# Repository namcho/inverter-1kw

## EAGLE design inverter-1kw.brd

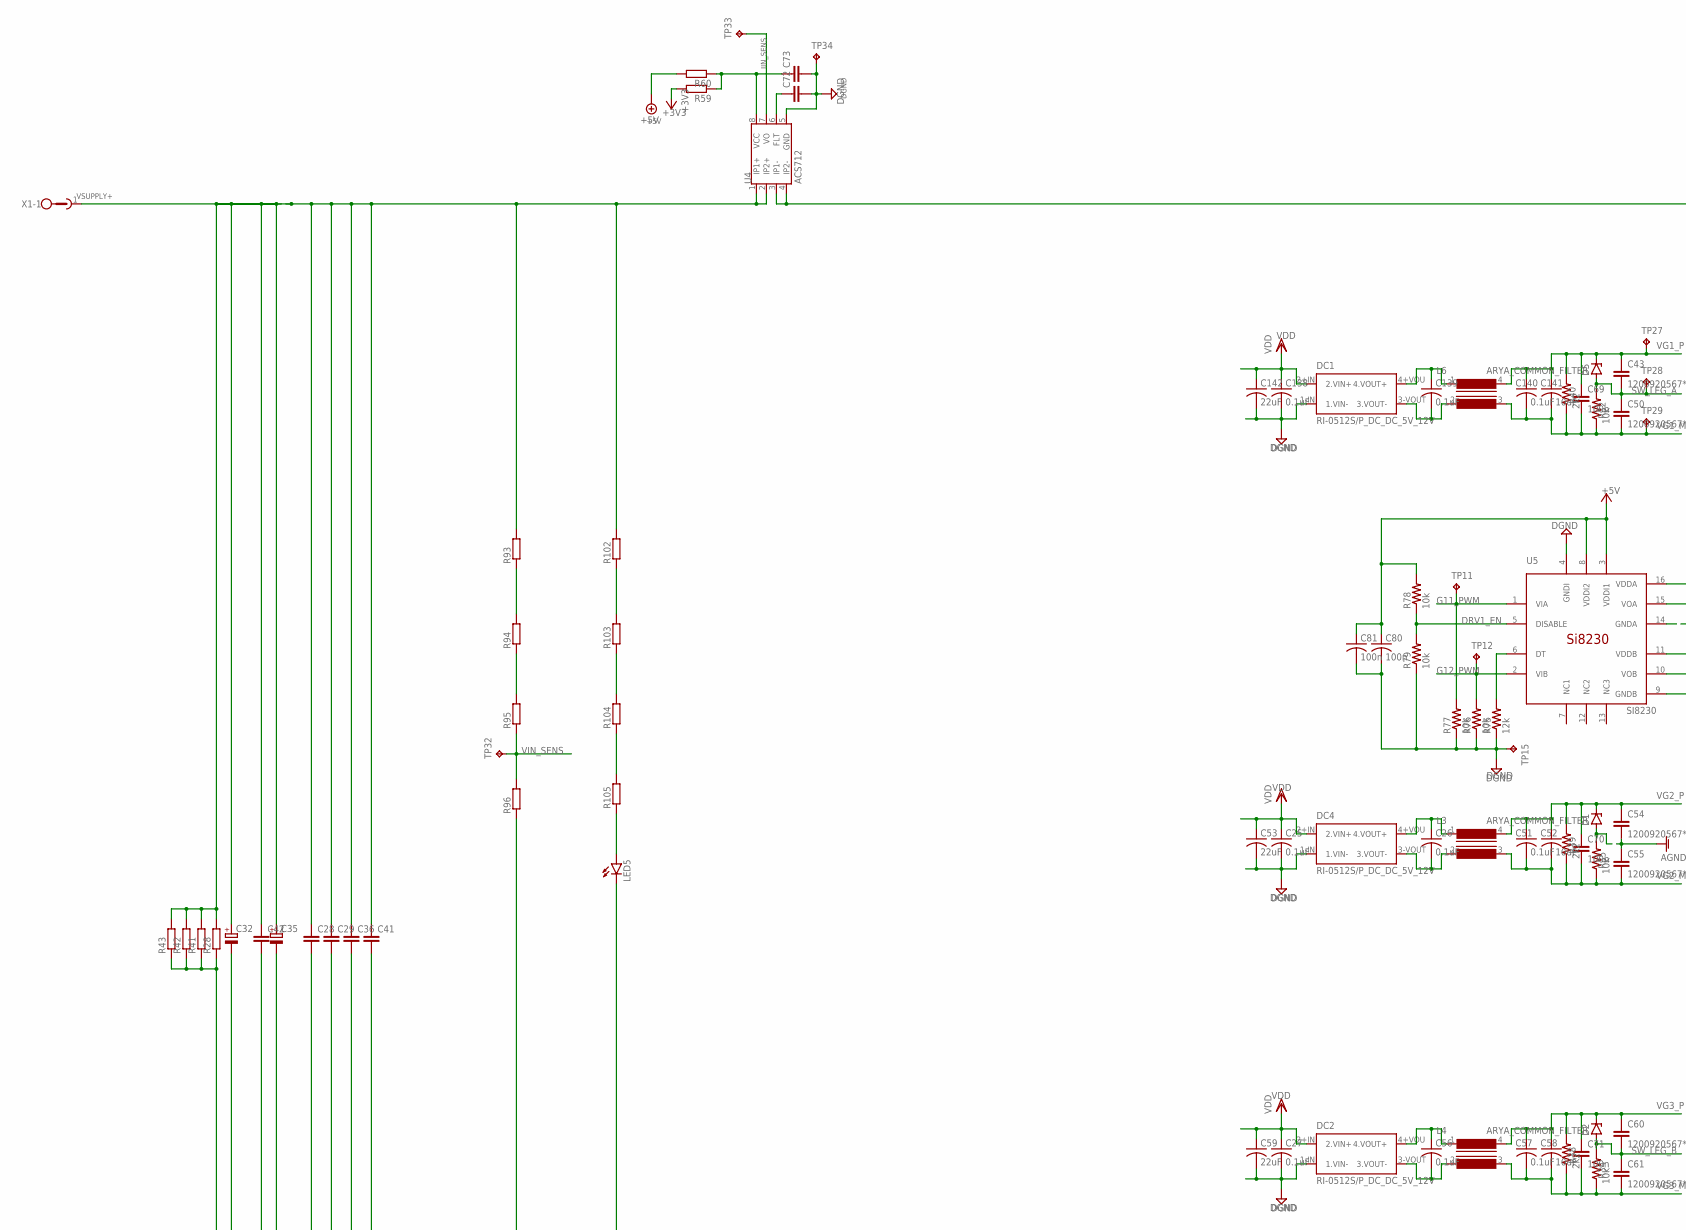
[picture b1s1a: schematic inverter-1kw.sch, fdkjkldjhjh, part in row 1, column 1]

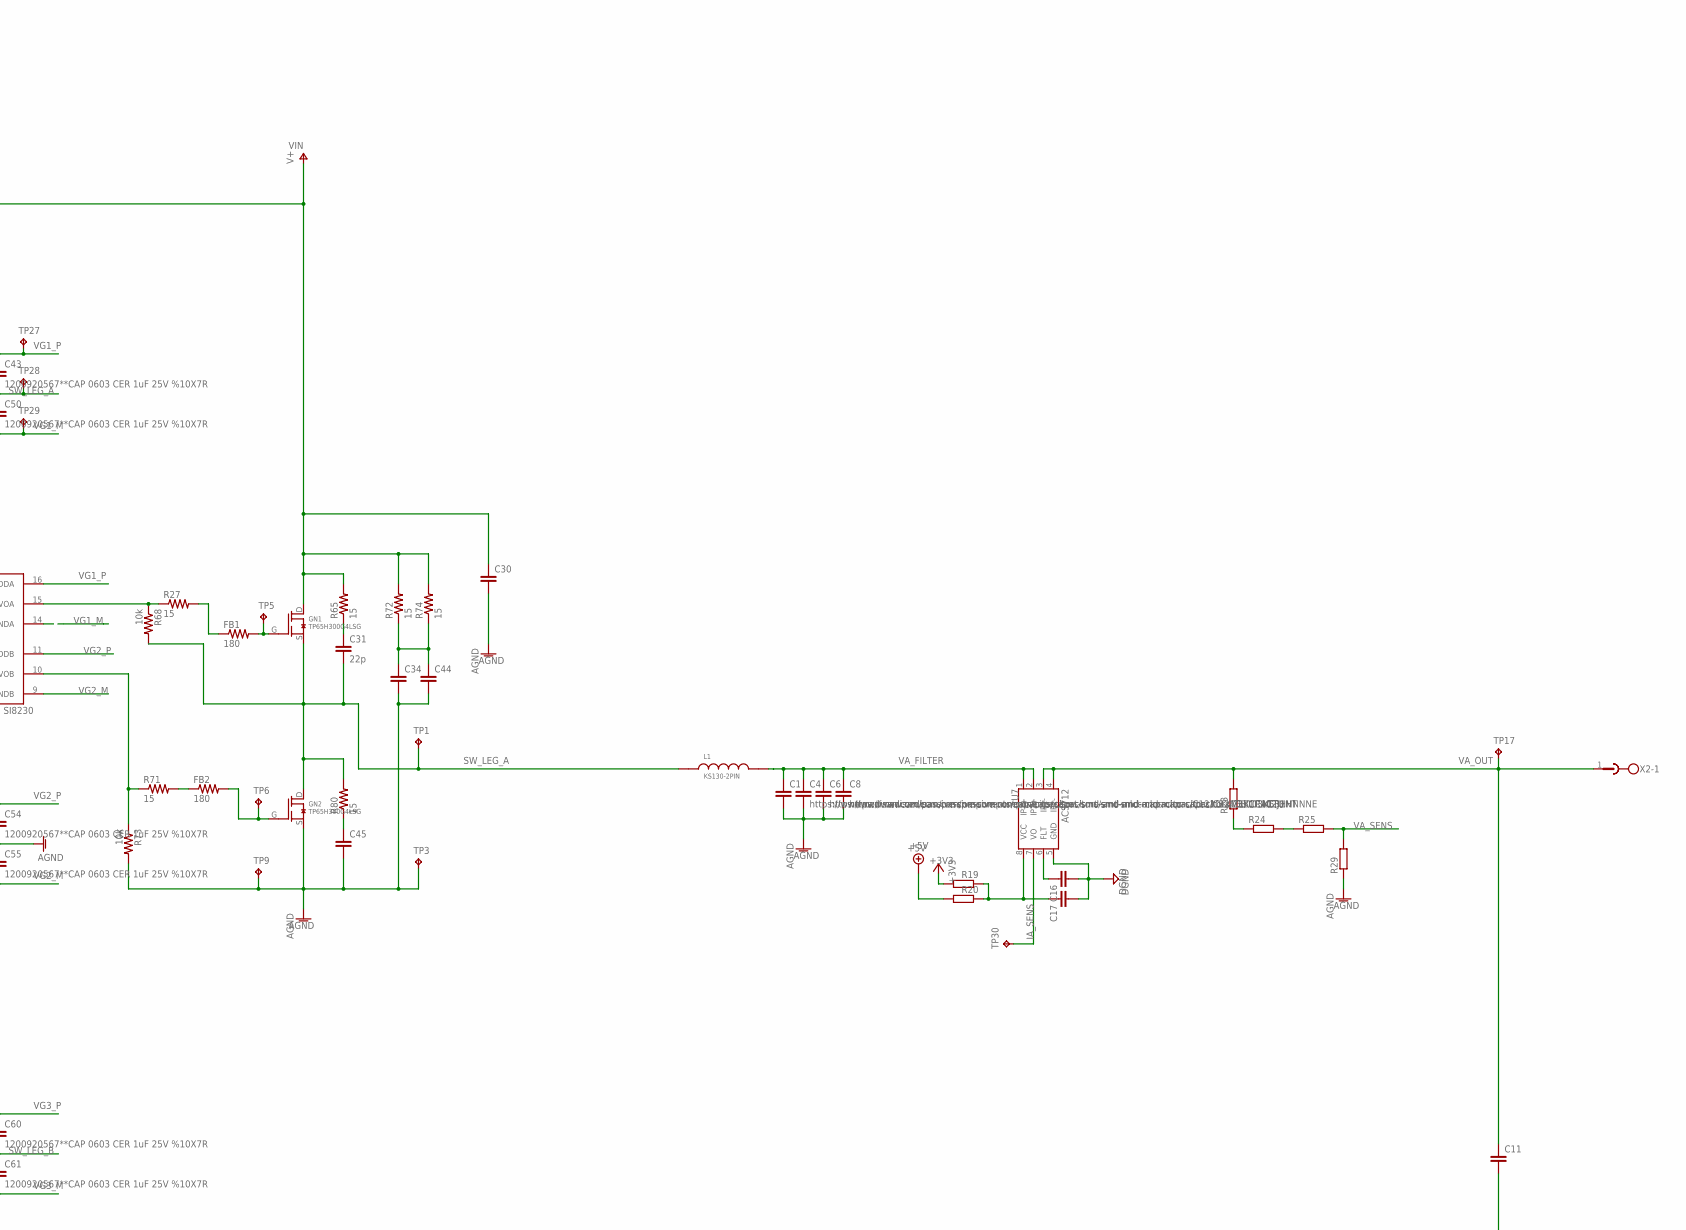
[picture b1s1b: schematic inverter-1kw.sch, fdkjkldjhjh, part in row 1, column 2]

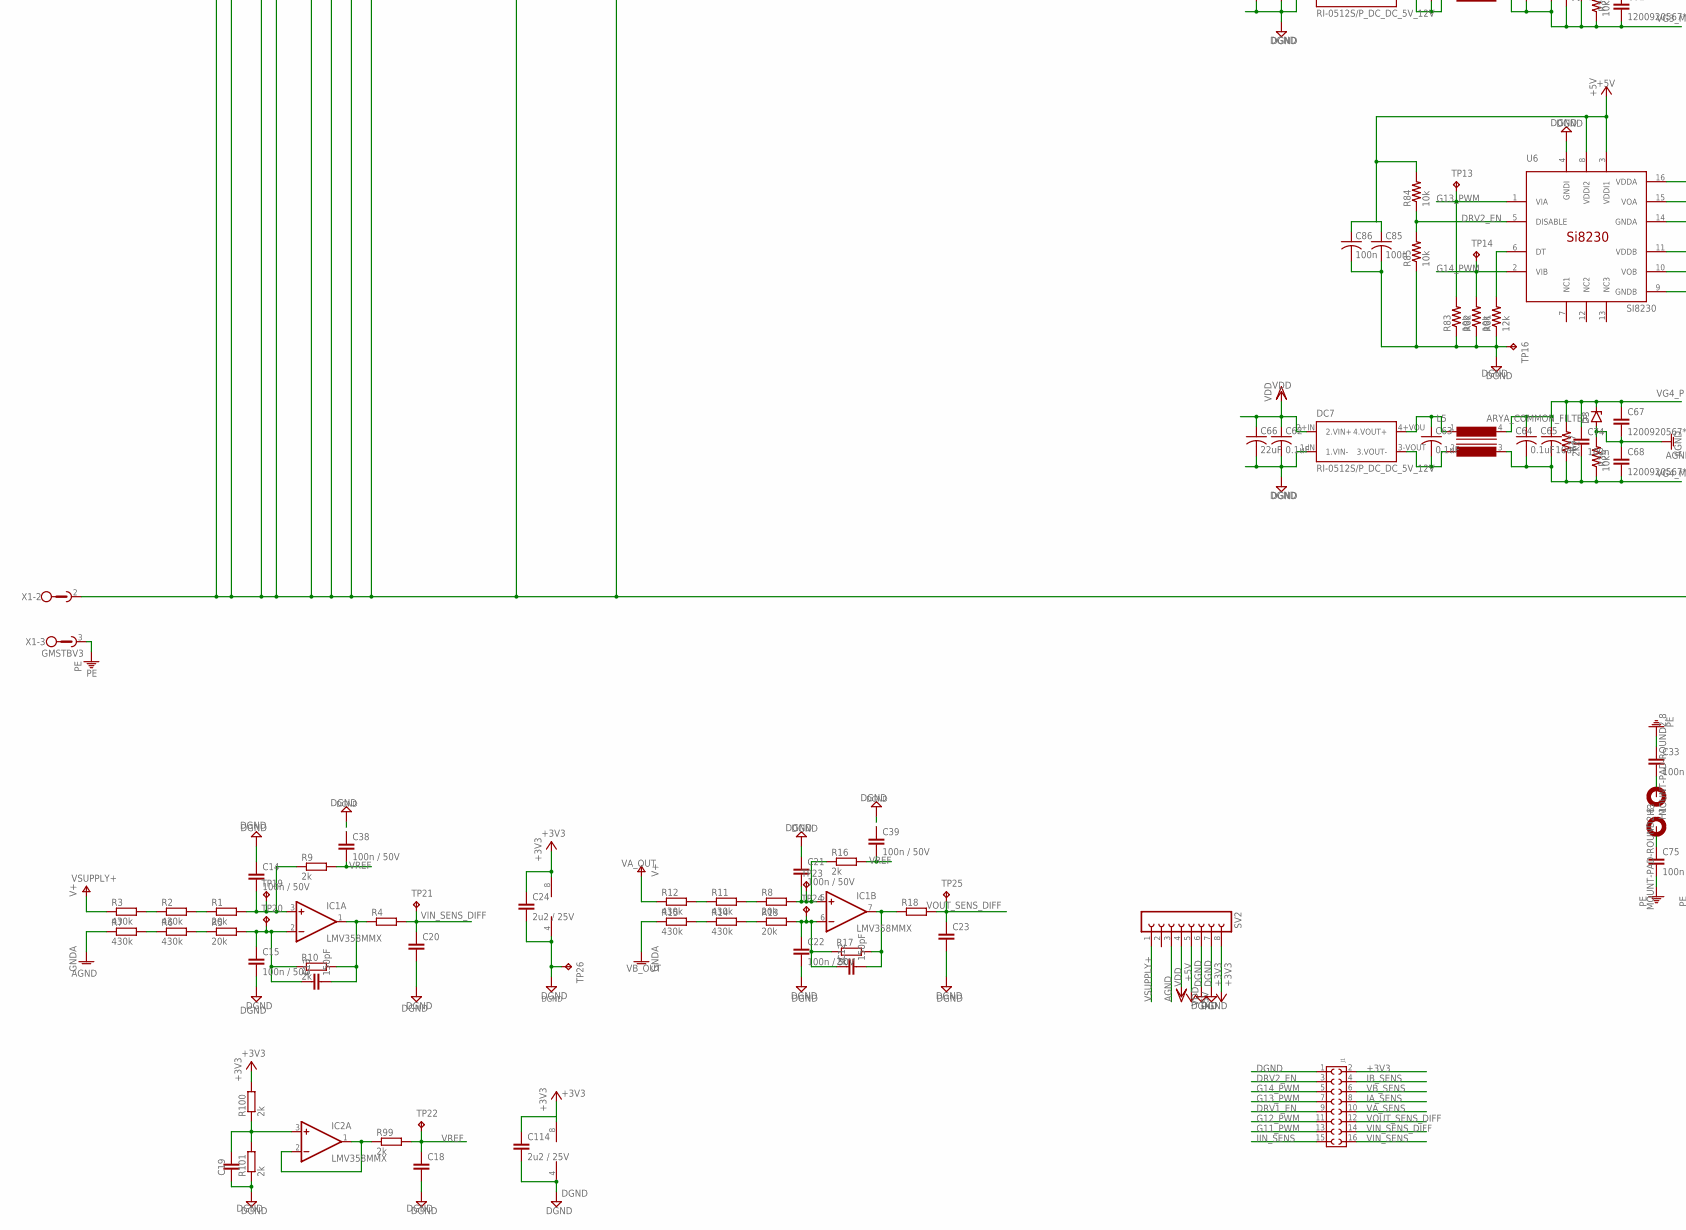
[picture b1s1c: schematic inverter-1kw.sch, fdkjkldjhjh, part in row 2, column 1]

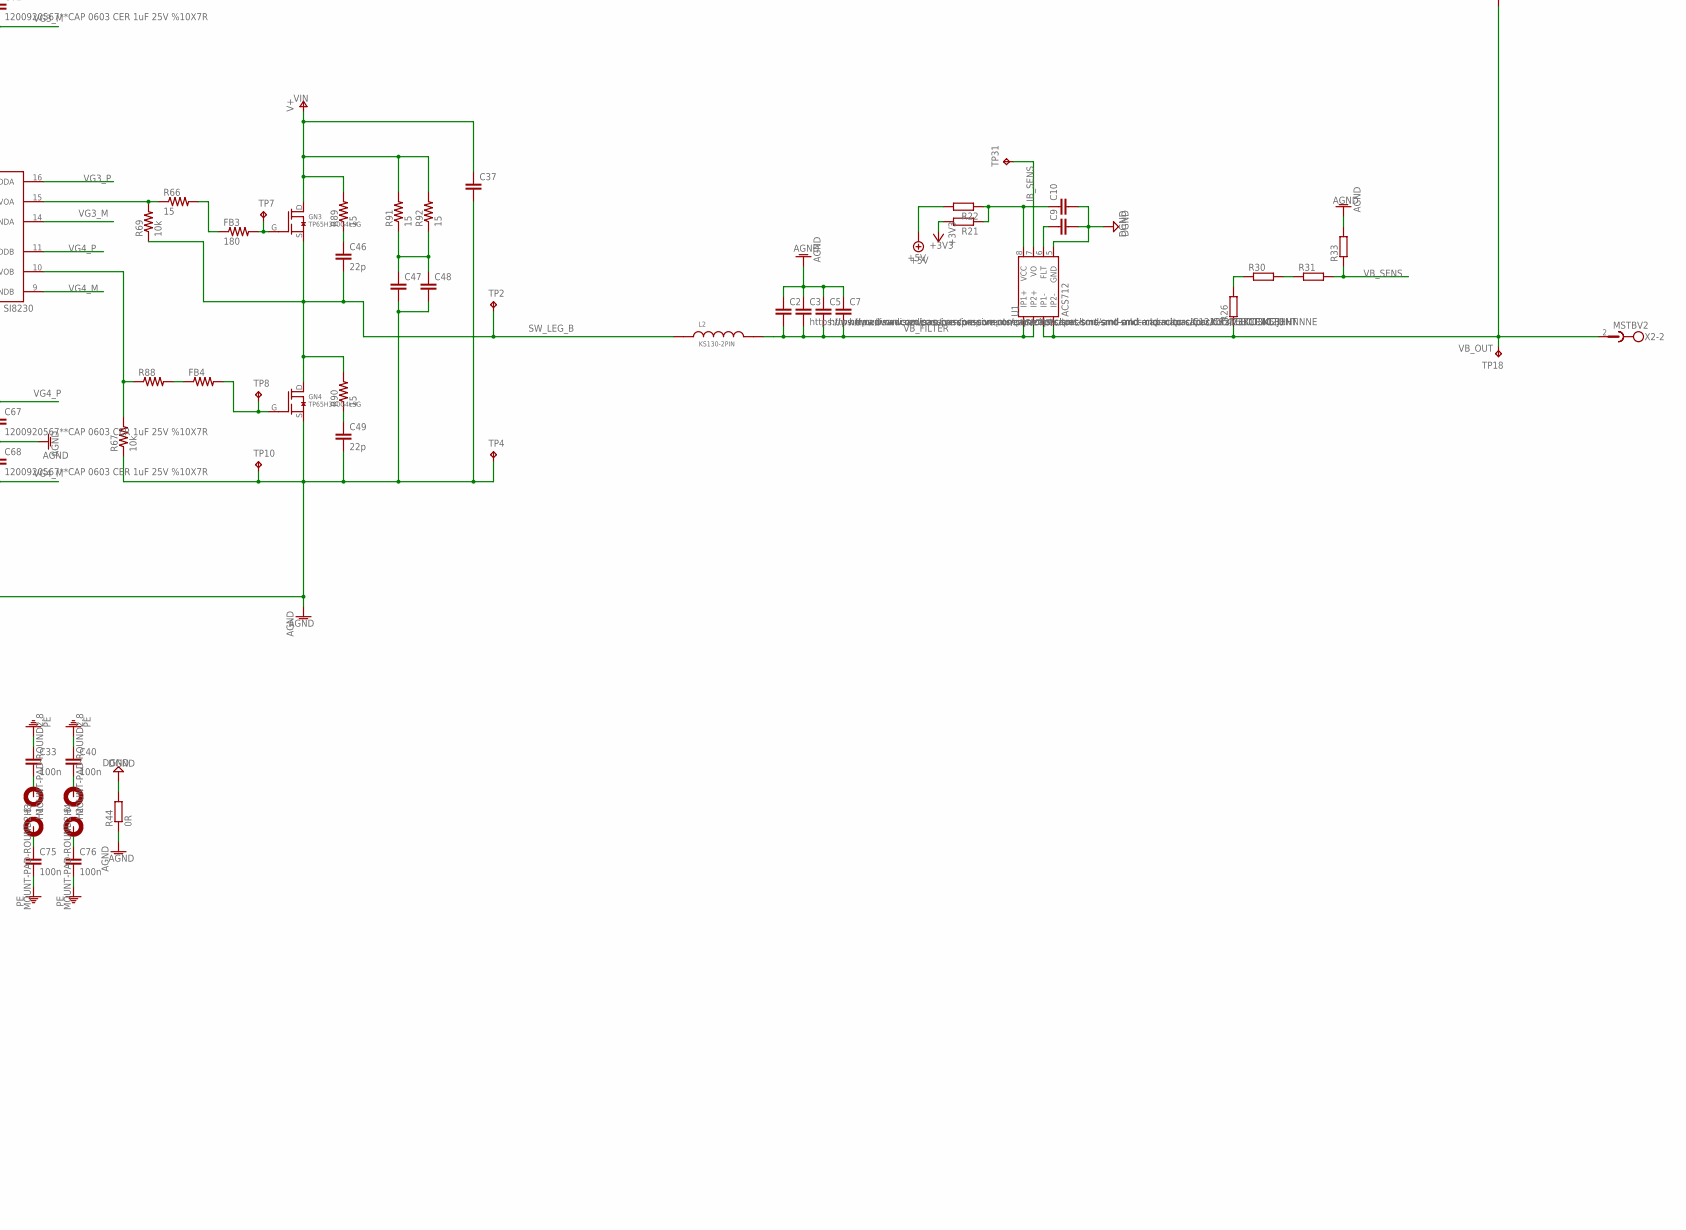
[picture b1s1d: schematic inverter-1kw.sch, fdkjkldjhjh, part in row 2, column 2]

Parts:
C1, C2: C-EUC2225K; C2225K
C3, C4: https://www.ozdisan.com/passive-components/capaci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; C1210K
C5, C6, C7, C8: https://www.ozdisan.com/passive-components/capaci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; C1206
C9, C10, C16, C17, C18, C19, C20, C23, C72, C73: C-EUC0603; C0603
C11: C27/17; C27.5B17
C12, C13: 150pF; C0603
C14, C15, C21, C22, C38, C39: 100n / 50V; C0603
C24, C114: 2u2 / 25V; C0603
C25, C26, C27, C51, C56, C57, C62, C63, C64, C138, C139, C140: 0.1uF; C0603
C28, C29, C30, C36, C37, C41, C42: C-EUC2220K; C2220K
C31, C46, C49: 22p; C1206
C32, C35: CPOL-EUE7.5-18; E7,5-18
C33, C40, C75, C76: 100n; C0805
C34, C44, C45, C47, C48: C-EUC1206; C1206
C43, C50, C54, C55, C60, C61, C67, C68: 1200920567**CAP 0603 CER 1uF 25V %10X7R; C0603K
C52, C58, C65, C141: 10uF; C0805
C53, C59, C66, C142: 22uF; C1206
C69, C70, C71, C74: 100n; C0603K
C80, C81, C85, C86: 100n; C0603
D1, D2, D3, D5: ZENER-DIODESOD80C; SOD80C
DC1, DC2, DC4, DC7: RI-0512S/P_DC_DC_5V_12V
FB1, FB2, FB3: 180; R0603
FB4: R-US_R0603; R0603
GN1, GN2, GN3, GN4: TP65H300G4LSG
H1, H2, H3, H4: MOUNT-PAD-ROUND2.8; 2,8-PAD
IC1, IC2: LMV358MMX; MSOP08
J1: 6230XX21021_62301621021; 62301621021
L1, L2: KS130-2PIN
L3, L4, L5, L6: ARYA_COMMON_FILTER
LED5: LEDCHIPLED_0805; CHIPLED_0805
R1, R5, R8, R13: 20k; R1206
R2, R3, R6, R7, R11, R12, R14, R15: 430k; R1206
R4, R18, R19, R20, R21, R22, R59, R60: R-EU_R0603; R0603
R9, R10, R16, R17, R99, R100, R101: 2k; R0603
R23, R24, R25, R26, R28, R29, R30, R31, R33, R41, R42, R43, R93, R94, R95, R96, R102, R103, R104, R105: R-EU_R1206; R1206
R27, R66, R71: 15; R0603
R32, R34, R35, R36, R67, R68, R69, R73, R76, R77, R78, R79, R82, R83, R84, R85: 10k; R0603
R37, R38, R39, R40: 2k2; R0603
R44: 0R; R1206
R65, R72, R74, R80, R89, R90, R91, R92: 15; R1206
R75, R81: 12k; R0603
R88: R-US_R0603; R0603
SV2: FE08-1; FE08
TP1, TP2, TP3, TP4, TP17, TP18: TPTP17R; TP17R
TP5, TP6, TP7, TP8, TP9, TP10, TP11, TP12, TP13, TP14, TP15, TP16, TP19, TP20, TP21, TP22, TP23, TP24, TP25, TP26, TP27, TP28, TP29, TP30, TP31, TP32, TP33, TP34: TPTP06R; TP06R
U1, U4, U7: ACS712; SOIC8
U5, U6: SI8230; SI8230-N
X1: GMSTBV3
X2: MSTBV2

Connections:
+3V3: C24.1, C114.1, IC1.8 (V+), IC2.8 (V+), J1.2, R19.2, R21.2, R59.2, R100.2, SV2.8
+5V: C80.1, C81.1, C85.1, C86.1, R20.2, R22.2, R60.2, R78.2, R84.2, SV2.5, U5.3 (VDDI1), U5.8 (VDDI2), U6.3 (VDDI1), U6.8 (VDDI2)
AGND: C1.2, C2.1, C3.1, C4.2, C5.1, C6.2, C7.1, C8.2, C28.2, C29.2, C30.2, C32.-, C34.2, C35.-, C36.2, C37.2, C41.2, C42.2, C44.2, C45.2, C47.2, C48.2, C49.2, C54.2, C55.1, C67.2, C68.1, D1.A, D3.A, GN2.S, GN4.S, LED5.C, R7.1, R28.1, R29.1, R33.2, R35.2, R36.2, R41.1, R42.1, R43.1, R44.1, R67.1, R73.2, R96.1, SV2.3, TP3.TP, TP4.TP, TP9.TP, TP10.TP, X1.2
DGND: C9.2, C10.2, C14.1, C15.2, C16.2, C17.2, C18.2, C19.2, C20.2, C21.1, C22.2, C23.2, C24.2, C25.2, C27.2, C38.1, C39.1, C53.2, C59.2, C62.2, C66.2, C72.2, C73.2, C80.2, C81.2, C85.2, C86.2, C114.2, C138.2, C142.2, DC1.1-IN (1.VIN-), DC2.1-IN (1.VIN-), DC4.1-IN (1.VIN-), DC7.1-IN (1.VIN-), IC1.4 (V-), IC2.4 (V-), J1.1, R44.2, R75.1, R76.1, R77.1, R79.1, R81.1, R82.1, R83.1, R85.1, R101.1, SV2.6, SV2.7, TP15.TP, TP16.TP, TP26.TP, TP34.TP, U1.5 (GND), U4.5 (GND), U5.4 (GNDI), U6.4 (GNDI), U7.5 (GND)
DRV1_EN: J1.9, R78.1, R79.2, U5.5 (DISABLE)
DRV2_EN: J1.3, R84.1, R85.2, U6.5 (DISABLE)
G11_PWM: J1.13, R77.2, TP11.TP, U5.1 (VIA)
G12_PWM: J1.11, R76.2, TP12.TP, U5.2 (VIB)
G13_PWM: J1.7, R83.2, TP13.TP, U6.1 (VIA)
G14_PWM: J1.5, R82.2, TP14.TP, U6.2 (VIB)
IA_SENS: J1.8, TP30.TP, U7.7 (VO)
IB_SENS: J1.4, TP31.TP, U1.7 (VO)
IIN_SENS: J1.15, TP33.TP, U4.7 (VO)
unnamed: C19.1, IC2.3 (+IN), R100.1, R101.2
unnamed: IC2.1 (OUT), IC2.2 (-IN), R99.1
unnamed: C26.1, DC4.4+VOU (4.VOUT+), L3.1
unnamed: R93.1, R94.2
unnamed: R75.2, U5.6 (DT)
unnamed: R23.1, R24.1
unnamed: C14.2, IC1.3 (+IN), R1.2, R9.1, TP19.TP
unnamed: C9.1, U1.6 (FLT)
unnamed: C13.1, C15.1, IC1.2 (-IN), R5.2, R10.1, TP20.TP
unnamed: R5.1, R6.2
unnamed: R6.1, R7.2
unnamed: R13.1, R14.2
unnamed: R14.1, R15.2
unnamed: C26.2, DC4.3-VOUT (3.VOUT-), L3.2
unnamed: R2.1, R3.2
unnamed: R1.1, R2.2
unnamed: R11.1, R12.2
unnamed: C13.2, IC1.1 (OUT), R4.1, R10.2
unnamed: R8.1, R11.2
unnamed: C21.2, IC1.5 (+IN), R8.2, R16.1, TP23.TP
unnamed: C16.1, U7.6 (FLT)
unnamed: C56.1, DC2.4+VOU (4.VOUT+), L4.1
unnamed: C12.1, C22.1, IC1.6 (-IN), R13.2, R17.1, TP24.TP
unnamed: C10.1, R21.1, R22.1, U1.8 (VCC)
unnamed: C12.2, IC1.7 (OUT), R17.2, R18.1
unnamed: R24.2, R25.1
unnamed: R26.2, R30.1
unnamed: R30.2, R31.1
unnamed: R27.1, R68.1, U5.15 (VOA)
unnamed: C17.1, R19.1, R20.1, U7.8 (VCC)
unnamed: R94.1, R95.2
unnamed: C56.2, DC2.3-VOUT (3.VOUT-), L4.2
unnamed: C63.1, DC7.4+VOU (4.VOUT+), L5.1
unnamed: FB1.1, R27.2
unnamed: FB1.2, GN1.G, TP5.TP
unnamed: FB3.1, R66.2
unnamed: FB3.2, GN3.G, TP7.TP
unnamed: C63.2, DC7.3-VOUT (3.VOUT-), L5.2
unnamed: C33.2, H1.B2,8
unnamed: C40.2, H2.B2,8
unnamed: C75.1, H3.B2,8
unnamed: C76.1, H4.B2,8
unnamed: R102.1, R103.2
unnamed: R103.1, R104.2
unnamed: R66.1, R69.2, U6.15 (VOA)
unnamed: R104.1, R105.2
unnamed: LED5.A, R105.1
unnamed: C73.1, R59.1, R60.1, U4.8 (VCC)
unnamed: C72.1, U4.6 (FLT)
unnamed: FB2.2, GN2.G, TP6.TP
unnamed: FB2.1, R71.2
unnamed: R71.1, R73.1, U5.10 (VOB)
unnamed: C34.1, C44.1, R72.1, R74.1
unnamed: C31.1, R65.1
unnamed: FB4.2, GN4.G, TP8.TP
unnamed: R81.2, U6.6 (DT)
unnamed: FB4.1, R88.2
unnamed: C45.1, R80.1
unnamed: R67.2, R88.1, U6.10 (VOB)
unnamed: C46.1, R89.1
unnamed: C49.1, R90.1
unnamed: C47.1, C48.1, R91.1, R92.1
unnamed: C139.1, DC1.4+VOU (4.VOUT+), L6.1
unnamed: C139.2, DC1.3-VOUT (3.VOUT-), L6.2
PE: C33.1, C40.1, C75.2, C76.2, X1.3
SW_LEG_A: C31.2, C43.2, C50.1, D5.A, GN1.S, GN2.D, L1.1, R32.2, R68.2, R80.2, TP1.TP, TP28.TP
SW_LEG_B: C46.2, C60.2, C61.1, D2.A, GN3.S, GN4.D, L2.1, R34.2, R69.1, R90.2, TP2.TP
VA_FILTER: C1.1, C4.1, C6.1, C8.1, L1.2, U7.1 (IP1+), U7.2 (IP2+)
VA_OUT: C11.1, R12.1, R23.2, TP17.TP, U7.3 (IP1-), U7.4 (IP2-), X2.1
VA_SENS: J1.10, R25.2, R29.2
VB_FILTER: C2.2, C3.2, C5.2, C7.2, L2.2, U1.1 (IP1+), U1.2 (IP2+)
VB_OUT: C11.2, R15.1, R26.1, TP18.TP, U1.3 (IP1-), U1.4 (IP2-), X2.2
VB_SENS: J1.6, R31.2, R33.1
VDD: C25.1, C27.1, C53.1, C59.1, C62.1, C66.1, C138.1, C142.1, DC1.2+IN (2.VIN+), DC2.2+IN (2.VIN+), DC4.2+IN (2.VIN+), DC7.2+IN (2.VIN+), SV2.4
VG1_M: C50.2, C69.2, C140.2, C141.2, L6.3, R32.1, R40.1, TP29.TP, U5.14 (GNDA)
VG1_P: C43.1, C69.1, C140.1, C141.1, D5.C, L6.4, R40.2, TP27.TP, U5.16 (VDDA)
VG2_M: C51.2, C52.2, C55.2, C70.2, L3.3, R35.1, R39.1, U5.9 (GNDB)
VG2_P: C51.1, C52.1, C54.1, C70.1, D1.C, L3.4, R39.2, U5.11 (VDDB)
VG3_M: C57.2, C58.2, C61.2, C71.2, L4.3, R34.1, R38.1, U6.14 (GNDA)
VG3_P: C57.1, C58.1, C60.1, C71.1, D2.C, L4.4, R38.2, U6.16 (VDDA)
VG4_M: C64.2, C65.2, C68.2, C74.2, L5.3, R36.1, R37.1, U6.9 (GNDB)
VG4_P: C64.1, C65.1, C67.1, C74.1, D3.C, L5.4, R37.2, U6.11 (VDDB)
VIN: C30.1, C37.1, GN1.D, GN3.D, R65.2, R72.2, R74.2, R89.2, R91.2, R92.2, U4.3 (IP1-), U4.4 (IP2-)
VIN_SENS: J1.16, R95.1, R96.2, TP32.TP
VIN_SENS_DIFF: C20.1, J1.14, R4.2, TP21.TP
VOUT_SENS_DIFF: C23.1, J1.12, R18.2, TP25.TP
VREF: C18.1, C38.2, C39.2, R9.2, R16.2, R99.2, TP22.TP
VSUPPLY+: C28.1, C29.1, C32.+, C35.+, C36.1, C41.1, C42.1, R3.1, R28.2, R41.2, R42.2, R43.2, R93.2, R102.2, SV2.1, U4.1 (IP1+), U4.2 (IP2+), X1.1

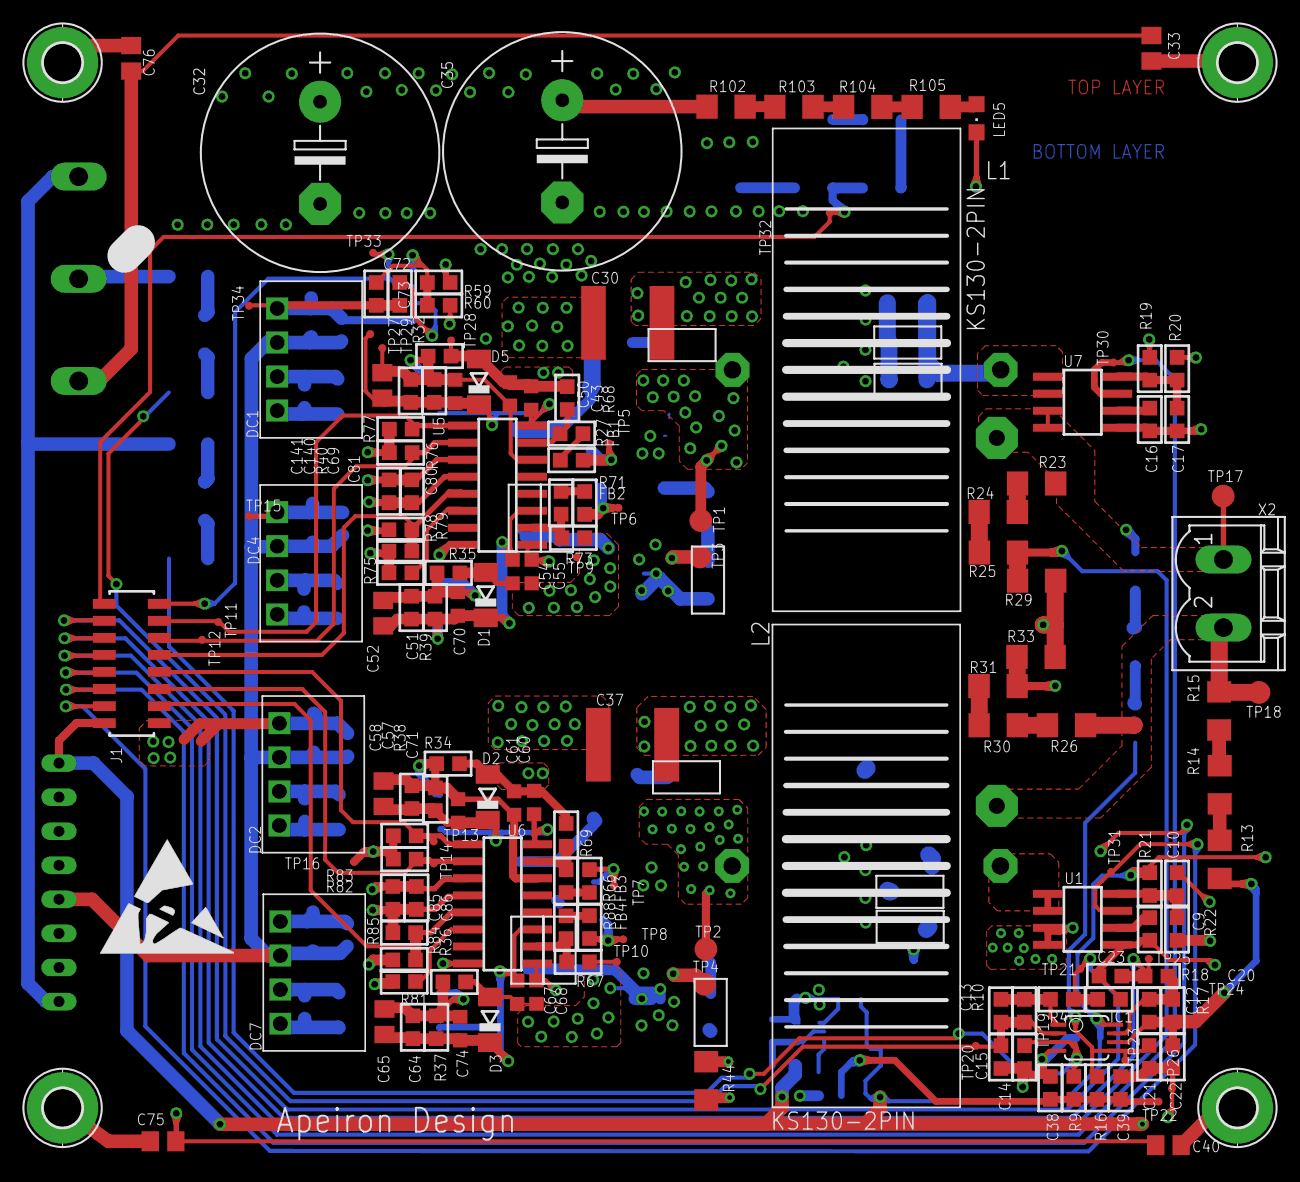
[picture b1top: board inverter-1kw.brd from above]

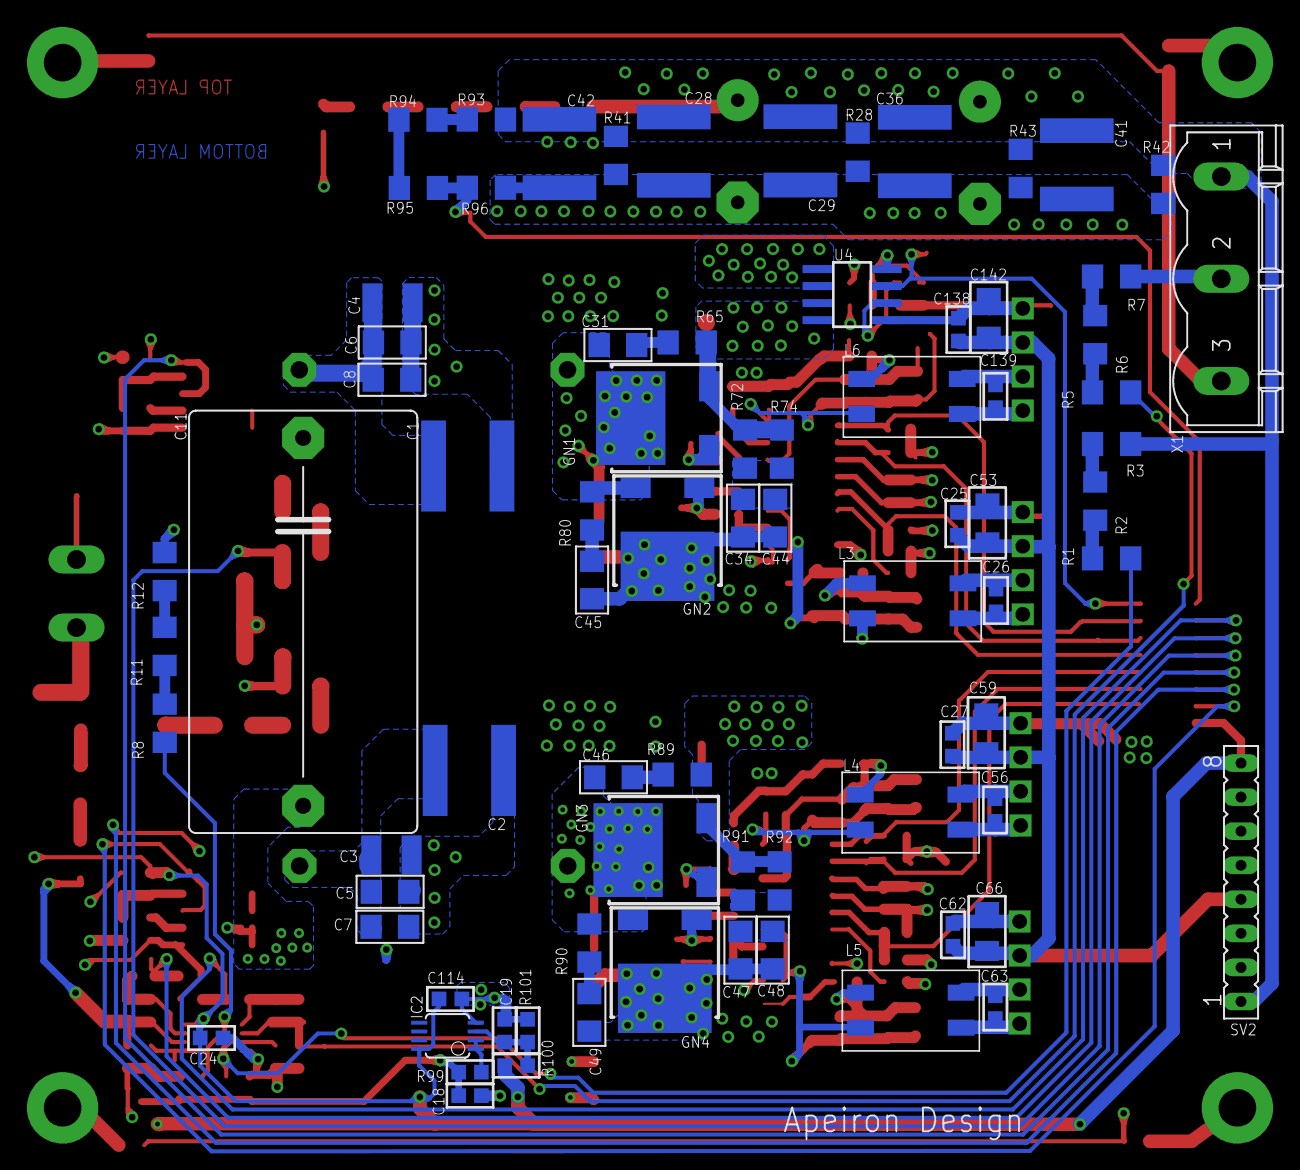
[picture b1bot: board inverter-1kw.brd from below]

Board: 5 copper layers, 241 parts (78 on the bottom side), 101 nets.

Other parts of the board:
U$1: ESD_10.00

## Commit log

2021-02-24 Proje olusturuldu.
2021-02-24 Brd dosyasi olusturuldu.
2021-02-25 Giriş kondansatörleri düzenlendi.
2021-02-25 Bobin paketleri guncellendi. Roleler ince secildi.
2021-02-25 Role beslemeleri VDD ile sembolize edildi.
2021-02-25 Cikis terminaline kondasator eklendi. Guc soketleri icin(4-pinli) kullanilacak urun linki value alanlarina yazildi.
2021-02-25 Opamp paketleri ve etrafindaki malzemeler kucultuldu.
2021-02-25 Kontrol karti soketleri eklendi.
    Giris beslemesini gostermek icin led eklentisi yapildi.
2021-02-25 Guc hattinda bulunmayan bir cok cap paketi 603 yapildi.
2021-02-26 ölçüm devresi ve röle kontrol devresi düzenlendi.
2021-03-01 Guc kati icin yerlesim yapildi.
2021-03-02 Guc kati yerlesim alani kucultuldu. 2 tane Cin silindi. Mosfet bulk kapasiteleri duzenlendi.
2021-03-03 Driver yerleşimi yapıldı.
2021-03-03 GS paralel 10k direncler Rg direncinin soluna alindi.
2021-03-03 1206 paket R ve C'ler editlenmis RCl kutuphanesinden cekildi.
2021-03-04 Driver yerleşimi iyileştirildi.
2021-03-04 Common Filter devresi düzenlendi
2021-03-04 ölçüm devreleri düzenlendi.
2021-03-05 Giris ve cikis guc terminalleri degistirildi.
2021-03-08 Filtre devresi ve opamp devresi düzenlendi.
2021-03-11 Opamp devresi düzenlendi
2021-03-11 İyileştirmeler yapıldı
2021-03-12 Soket baglantilari duzenlendi. B kol mosfetin AGND baglantisi duzeltildi.
2021-03-12 Düzenlemeler yapıldı.
2021-03-15 ölçüm devresi düzenlendi
2021-03-17 Giris ve giris terminalleri soket yapildi. Ganlarin dibindeki capler sadelestirildi.
2021-03-17 gitignore guncellendi.
2021-03-31 Negatif gerilim ihtiyacindan dolayi her bir ganfet icin izole DC-DC eklendi.
    DC-DC gate-driver besleme gerilimleri VDD'ye baglandi.
    Filtre bobinleri icin KS130 toroid nuvesi eklendi.
2021-03-31 Driver ve filtre devresi yerleşimleri yapıldı.
2021-03-31 Giriş kapasiteleri düzenlendi.
2021-04-02 Opamp devresi yerleşimi yapıldı
2021-04-02 opamp devresi iyileştirildi
2021-04-02 Test padler eklendi. Kart destek noktalariyla toprak arasina kondansatorler eklendi.
    Cin desarji icin kullanilacak direnc icin 4adet 1206 eklendi.
2021-04-09 bağlantıların bir kısmı yapıldı.
2021-04-15 Planeler yapıldı
2021-04-21 planler yapıldı tekrar
2021-04-21 Kontrol karti soketi SMD yapildi, guc giris soketi ve guc-karti soketi bottom-layer'a alindi.
2021-04-26 Planeler tamamlandı.
2021-04-29 3v3 kalınlaştırıldı, soket GND si plane yapıldı
2021-04-29 R3'un eksik baglantisi yapildi. 8'li besleme karti giris gerilimi baglantisi yapildi.
2021-04-29 Düzenlemeler yapıldı
2021-05-03 son hali
2021-05-03 Teardrops yapıldı
2021-05-04 Gerilim bölücü dirençleri kaynağa yakınlaştırıldı.
2021-05-04 Kontrol karti soketi wurth'den secildi.
2021-05-04 planeler düzenlendi.
2021-05-05 Finish
2021-06-16 Gerber dosyalari ve gerberi ürettigimiz brd dosyasi eklendi.

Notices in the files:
parts and their libraries:
Eagle_WR-PHD: Copyright: Würth Elektronik
